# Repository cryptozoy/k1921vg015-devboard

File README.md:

# К1921ВГ015 DEVBOARD

Проект печатной платы для микроконтроллера К1921ВГ015 разработанный в KiCad 9.

Пожалуйста учитывайте, что фото может незначительно отличаться от платы в проекте, поскольку туда могут вноситься мелкие исправления.

Если вы хотите последнюю версию гербер файлов - рекомендуется формировать их самим, что гарантирует их актуальность.

Файлы сверловки экспортированы с настройками по умолчанию и лежат в `/gerber/`

Требования для 5$ в nextPCB были учтены и лично мной проверены.

Огромное спасибо: [@cryptozoy](https://github.com/cryptozoy) за доработку платы.

Все пины контроллера задействованы, все функциональные пины выведены на гребёнки:

 - Порты ABC

 - Функциональные пины и коммуникация

Файлы для генерации пинаутов лежат в папке `pinouts`

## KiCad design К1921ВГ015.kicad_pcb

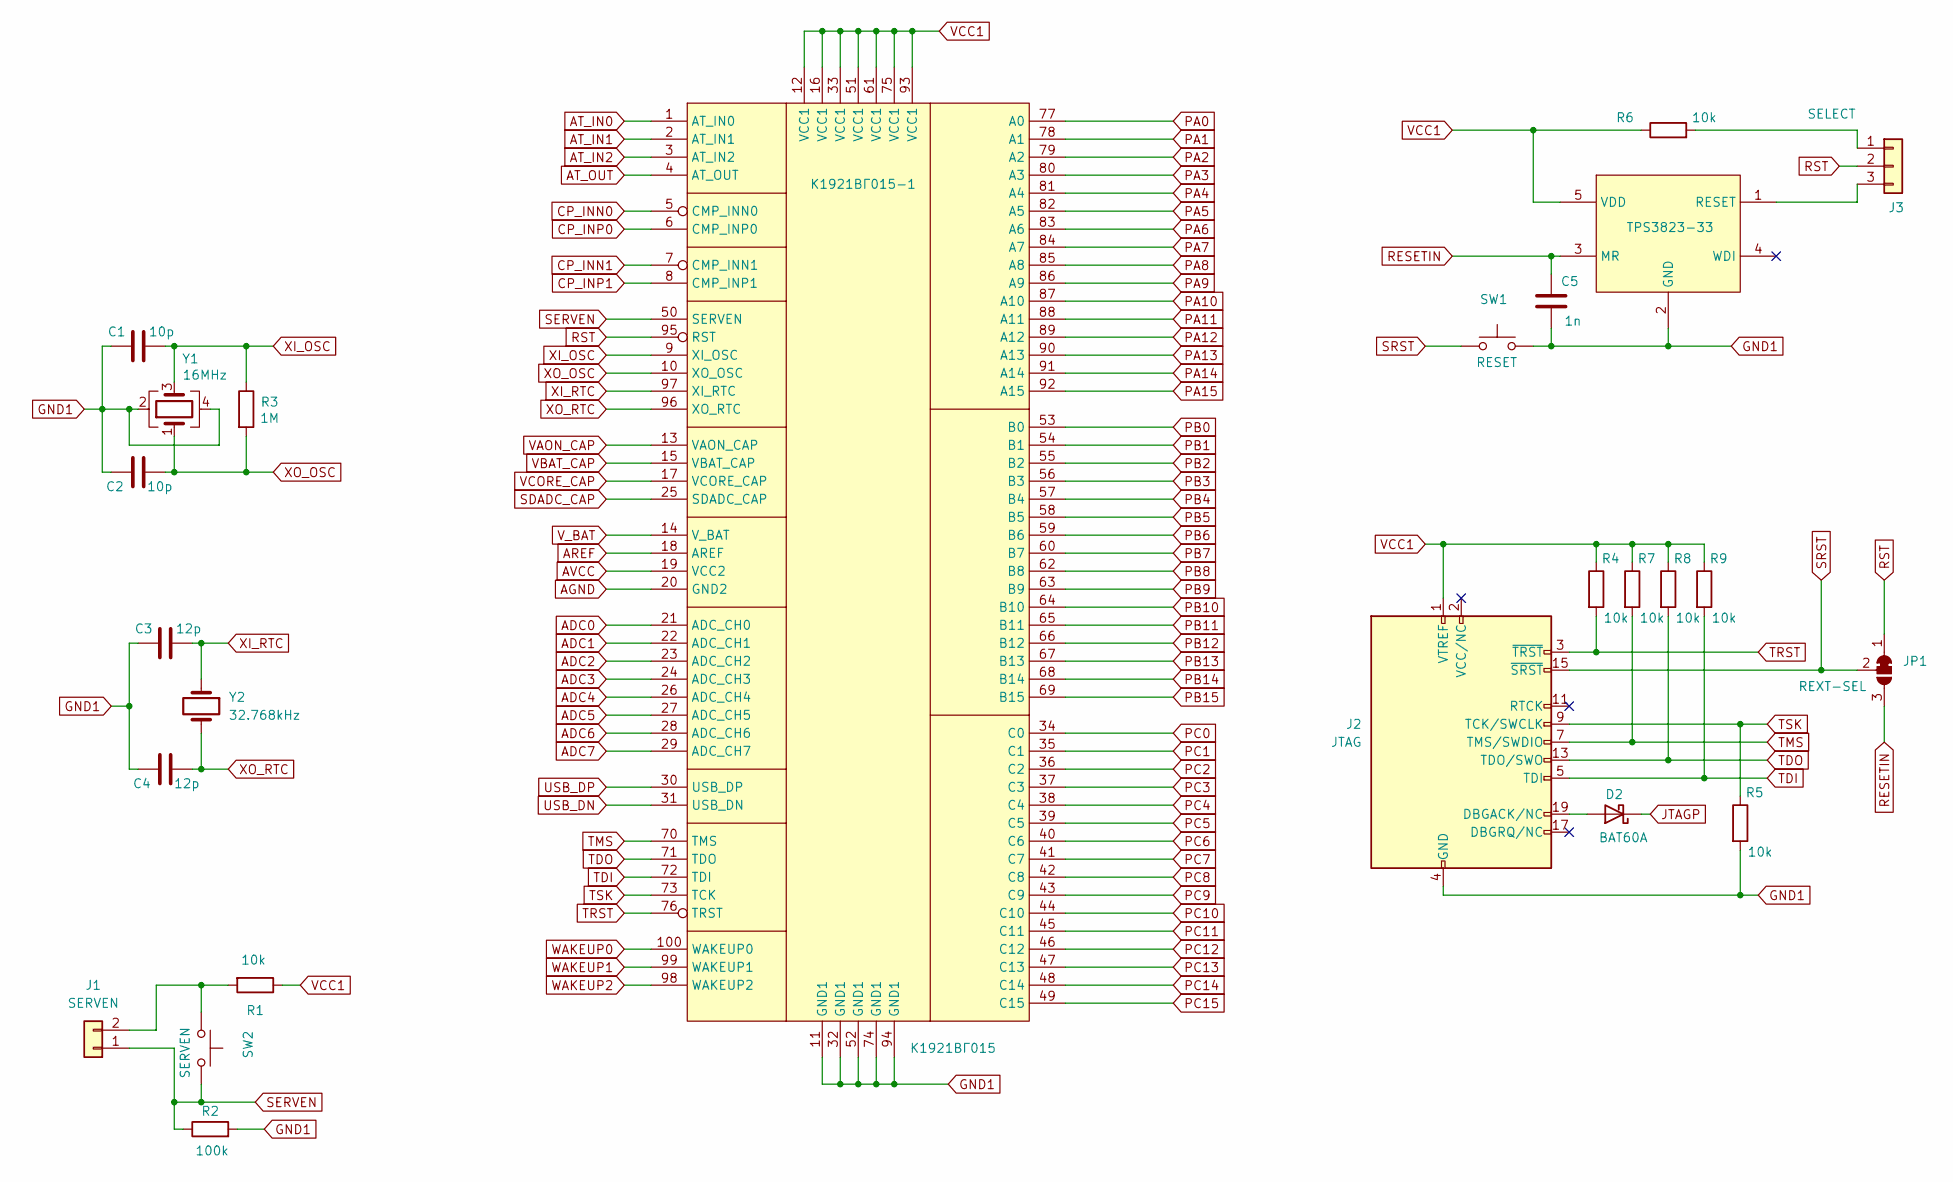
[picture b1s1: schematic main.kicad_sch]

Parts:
C1, C2: 10p; C_0805_2012Metric
C3, C4: 12p; C_0805_2012Metric
C5: 1n; C_0805_2012Metric
D2: BAT60A; D_SOD-323
J1: SERVEN; PinHeader_1x02_P2.54mm_Vertical
J2: JTAG; PinHeader_2x10_P2.54mm_Vertical
J3: SELECT; PinHeader_1x03_P2.54mm_Vertical
JP1: REXT-SEL; SolderJumper-3_P2.0mm_Open_TrianglePad1.0x1.5mm
R1, R4, R5, R6, R7, R8, R9: 10k; R_0805_2012Metric
R2: 100k; R_0805_2012Metric
R3: 1M; R_0805_2012Metric
SW1: RESET; SW_SPST_PTS647_Sx38
SW2: SERVEN; SW_SPST_PTS647_Sx38
TPS3823-1: TPS3823-33; SOT-23-5
Y1: 16MHz; Crystal_SMD_3225-4Pin_3.2x2.5mm
Y2: 32.768kHz; Crystal_SMD_3215-2Pin_3.2x1.5mm
К1921ВГ015-1: К1921ВГ015; LQFP-100_14x14mm_P0.5mm

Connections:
ADC0: К1921ВГ015-1.21 (ADC_CH0); also elsewhere on the board
ADC1: К1921ВГ015-1.22 (ADC_CH1); also elsewhere on the board
ADC2: К1921ВГ015-1.23 (ADC_CH2); also elsewhere on the board
ADC3: К1921ВГ015-1.24 (ADC_CH3); also elsewhere on the board
ADC4: К1921ВГ015-1.26 (ADC_CH4); also elsewhere on the board
ADC5: К1921ВГ015-1.27 (ADC_CH5); also elsewhere on the board
ADC6: К1921ВГ015-1.28 (ADC_CH6); also elsewhere on the board
ADC7: К1921ВГ015-1.29 (ADC_CH7); also elsewhere on the board
AGND: К1921ВГ015-1.20 (GND2); also elsewhere on the board
AREF: К1921ВГ015-1.18 (AREF); also elsewhere on the board
AT_IN0: К1921ВГ015-1.1 (AT_IN0); also elsewhere on the board
AT_IN1: К1921ВГ015-1.2 (AT_IN1); also elsewhere on the board
AT_IN2: К1921ВГ015-1.3 (AT_IN2); also elsewhere on the board
AT_OUT: К1921ВГ015-1.4 (AT_OUT); also elsewhere on the board
AVCC: К1921ВГ015-1.19 (VCC2); also elsewhere on the board
CAN0_RX: К1921ВГ015-1.42 (C8); also elsewhere on the board
CAN0_TX: К1921ВГ015-1.43 (C9); also elsewhere on the board
CAN1_RX: К1921ВГ015-1.44 (C10); also elsewhere on the board
CAN1_TX: К1921ВГ015-1.45 (C11); also elsewhere on the board
CP_INN0: К1921ВГ015-1.5 (CMP_INN0); also elsewhere on the board
CP_INN1: К1921ВГ015-1.7 (CMP_INN1); also elsewhere on the board
CP_INP0: К1921ВГ015-1.6 (CMP_INP0); also elsewhere on the board
CP_INP1: К1921ВГ015-1.8 (CMP_INP1); also elsewhere on the board
GND1: C1.2, C2.2, C3.2, C4.2, C5.2, J2.4 (GND), J2.6 (GND), J2.8 (GND), J2.10 (GND), J2.12 (GND), J2.14 (GND), J2.16 (GND), J2.18 (GND), J2.20 (GND), R2.2, R5.2, SW1.2, TPS3823-1.2 (GND), Y1.2, Y1.4, К1921ВГ015-1.11 (GND1), К1921ВГ015-1.32 (GND1), К1921ВГ015-1.52 (GND1), К1921ВГ015-1.74 (GND1), К1921ВГ015-1.94 (GND1); also elsewhere on the board
I2C_SCL: К1921ВГ015-1.46 (C12); also elsewhere on the board
I2C_SDA: К1921ВГ015-1.47 (C13); also elsewhere on the board
unnamed: D2.2 (A), J2.19 (DBGACK/NC)
unnamed: J1.2, R1.2, SW2.1
unnamed: J3.1, R6.2
unnamed: J3.3, TPS3823-1.1 (RESET)
PA0: К1921ВГ015-1.77 (A0); also elsewhere on the board
PA1: К1921ВГ015-1.78 (A1); also elsewhere on the board
PA2: К1921ВГ015-1.79 (A2); also elsewhere on the board
PA3: К1921ВГ015-1.80 (A3); also elsewhere on the board
PA4: К1921ВГ015-1.81 (A4); also elsewhere on the board
PA5: К1921ВГ015-1.82 (A5); also elsewhere on the board
PA6: К1921ВГ015-1.83 (A6); also elsewhere on the board
PA7: К1921ВГ015-1.84 (A7); also elsewhere on the board
PA8: К1921ВГ015-1.85 (A8); also elsewhere on the board
PA9: К1921ВГ015-1.86 (A9); also elsewhere on the board
PA10: К1921ВГ015-1.87 (A10); also elsewhere on the board
PA11: К1921ВГ015-1.88 (A11); also elsewhere on the board
PA12: К1921ВГ015-1.89 (A12); also elsewhere on the board
PA13: К1921ВГ015-1.90 (A13); also elsewhere on the board
PA14: К1921ВГ015-1.91 (A14); also elsewhere on the board
PA15: К1921ВГ015-1.92 (A15); also elsewhere on the board
PB0: К1921ВГ015-1.53 (B0); also elsewhere on the board
PB1: К1921ВГ015-1.54 (B1); also elsewhere on the board
PB2: К1921ВГ015-1.55 (B2); also elsewhere on the board
PB3: К1921ВГ015-1.56 (B3); also elsewhere on the board
PB4: К1921ВГ015-1.57 (B4); also elsewhere on the board
PB5: К1921ВГ015-1.58 (B5); also elsewhere on the board
PB6: К1921ВГ015-1.59 (B6); also elsewhere on the board
PB7: К1921ВГ015-1.60 (B7); also elsewhere on the board
PB8: К1921ВГ015-1.62 (B8); also elsewhere on the board
PB9: К1921ВГ015-1.63 (B9); also elsewhere on the board
PB10: К1921ВГ015-1.64 (B10); also elsewhere on the board
PB11: К1921ВГ015-1.65 (B11); also elsewhere on the board
PB12: К1921ВГ015-1.66 (B12); also elsewhere on the board
PB13: К1921ВГ015-1.67 (B13); also elsewhere on the board
PB14: К1921ВГ015-1.68 (B14); also elsewhere on the board
PB15: К1921ВГ015-1.69 (B15); also elsewhere on the board
PC0: К1921ВГ015-1.34 (C0); also elsewhere on the board
PC1: К1921ВГ015-1.35 (C1); also elsewhere on the board
PC2: К1921ВГ015-1.36 (C2); also elsewhere on the board
PC3: К1921ВГ015-1.37 (C3); also elsewhere on the board
PC4: К1921ВГ015-1.38 (C4); also elsewhere on the board
PC5: К1921ВГ015-1.39 (C5); also elsewhere on the board
PC6: К1921ВГ015-1.40 (C6); also elsewhere on the board
PC7: К1921ВГ015-1.41 (C7); also elsewhere on the board
PC14: К1921ВГ015-1.48 (C14); also elsewhere on the board
PC15: К1921ВГ015-1.49 (C15); also elsewhere on the board
PJTAG: D2.1 (K); also elsewhere on the board
RESETIN: C5.1, JP1.3 (B), TPS3823-1.3 (MR)
RST: J3.2, JP1.1 (A), К1921ВГ015-1.95 (RST)
SDADC_CAP: К1921ВГ015-1.25 (SDADC_CAP); also elsewhere on the board
SERVEN: J1.1, R2.1, SW2.2, К1921ВГ015-1.50 (SERVEN)
SRST: J2.15 (~SRST), JP1.2 (C), SW1.1
TDI: J2.5 (TDI), R9.2, К1921ВГ015-1.72 (TDI)
TDO: J2.13 (TDO/SWO), R8.2, К1921ВГ015-1.71 (TDO)
TMS: J2.7 (TMS/SWDIO), R7.2, К1921ВГ015-1.70 (TMS)
TRST: J2.3 (~TRST), R4.2, К1921ВГ015-1.76 (TRST)
TSK: J2.9 (TCK/SWCLK), R5.1, К1921ВГ015-1.73 (TCK)
USB_DN: К1921ВГ015-1.31 (USB_DN); also elsewhere on the board
USB_DP: К1921ВГ015-1.30 (USB_DP); also elsewhere on the board
VAON_CAP: К1921ВГ015-1.13 (VAON_CAP); also elsewhere on the board
VBAT_CAP: К1921ВГ015-1.15 (VBAT_CAP); also elsewhere on the board
VCC1: J2.1 (VTREF), R1.1, R4.1, R6.1, R7.1, R8.1, R9.1, TPS3823-1.5 (VDD), К1921ВГ015-1.12 (VCC1), К1921ВГ015-1.16 (VCC1), К1921ВГ015-1.33 (VCC1), К1921ВГ015-1.51 (VCC1), К1921ВГ015-1.61 (VCC1), К1921ВГ015-1.75 (VCC1), К1921ВГ015-1.93 (VCC1); also elsewhere on the board
VCORE_CAP: К1921ВГ015-1.17 (VCORE_CAP); also elsewhere on the board
V_BAT: К1921ВГ015-1.14 (V_BAT); also elsewhere on the board
WAKEUP0: К1921ВГ015-1.100 (WAKEUP0); also elsewhere on the board
WAKEUP1: К1921ВГ015-1.99 (WAKEUP1); also elsewhere on the board
WAKEUP2: К1921ВГ015-1.98 (WAKEUP2); also elsewhere on the board
XI_OSC: C1.1, R3.1, Y1.3, К1921ВГ015-1.9 (XI_OSC)
XI_RTC: C3.1, Y2.1, К1921ВГ015-1.97 (XI_RTC)
XO_OSC: C2.1, R3.2, Y1.1, К1921ВГ015-1.10 (XO_OSC)
XO_RTC: C4.1, Y2.2, К1921ВГ015-1.96 (XO_RTC)

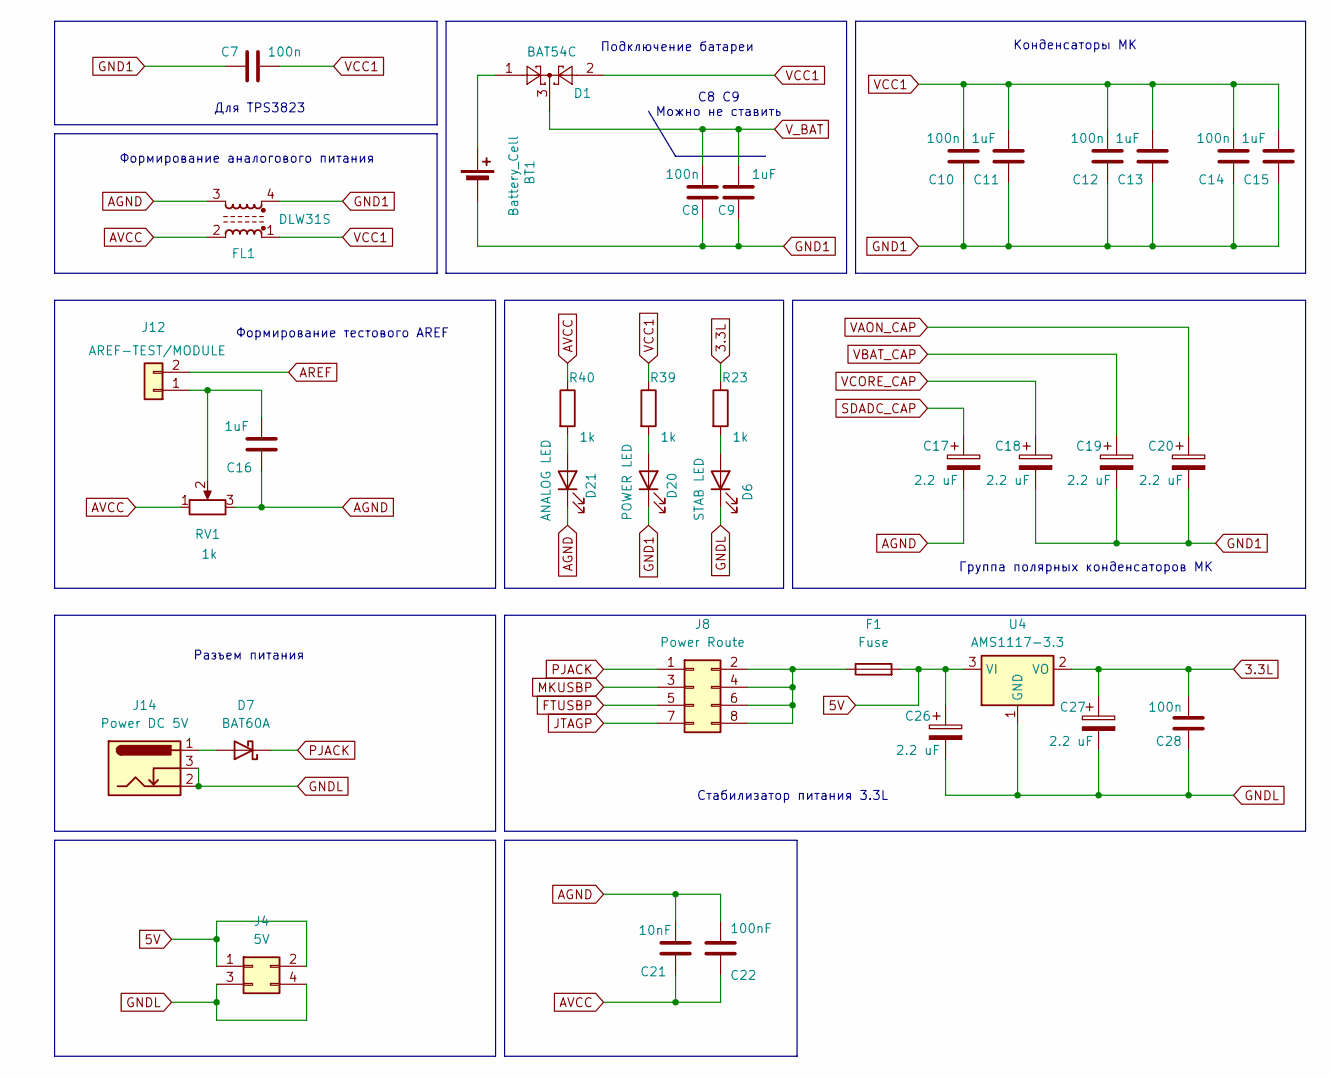
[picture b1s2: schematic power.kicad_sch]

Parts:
BT1: Battery_Cell; Battery_Panasonic_CR2032-HFN_Horizontal_CircularHoles
C7, C8, C10, C12, C14, C28: 100n; C_0805_2012Metric
C9, C11, C13, C15, C16: 1uF; C_0805_2012Metric
C17, C18, C19, C20, C26, C27: 2.2 uF; CP_EIA-3528-21_Kemet-B
C21: 10nF; C_0805_2012Metric
C22: 100nF; C_0805_2012Metric
D1: BAT54C; SOT-23
D6: STAB LED; LED_0805_2012Metric
D7: BAT60A; D_SOD-323
D20: POWER LED; LED_0805_2012Metric
D21: ANALOG LED; LED_0805_2012Metric
F1: Fuse; Fuse_1812_4532Metric
FL1: DLW31S; L_CommonMode_Wurth_WE-CNSW-1206
J4: 5V; PinHeader_2x02_P2.54mm_Vertical
J8: Power Route; PinHeader_2x04_P2.54mm_Vertical
J12: AREF-TEST/MODULE; PinHeader_1x02_P2.54mm_Vertical
J14: Power DC 5V; BarrelJack_GCT_DCJ200-10-A_Horizontal
R23, R39, R40: 1k; R_0805_2012Metric
RV1: 1k; Potentiometer_Bourns_3296W_Vertical
U4: AMS1117-3.3; SOT-223-3_TabPin2

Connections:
3.3L: C27.1, C28.1, R23.1, U4.2 (VO); also elsewhere on the board
5V: C26.1, F1.2, J4.1, J4.2, U4.3 (VI)
AGND: C16.2, C17.2, C21.1, C22.1, D21.1 (K), FL1.3, RV1.3; also elsewhere on the board
AREF: J12.2; also elsewhere on the board
AVCC: C21.2, C22.2, FL1.2, R40.1, RV1.1; also elsewhere on the board
FTUSBP: J8.5; also elsewhere on the board
GND1: BT1.2 (-), C7.2, C8.2, C9.2, C10.2, C11.2, C12.2, C13.2, C14.2, C15.2, C18.2, C19.2, C20.2, D20.1 (K), FL1.4; also elsewhere on the board
GNDL: C26.2, C27.2, C28.2, D6.1 (K), J4.3, J4.4, J14.2, J14.3, U4.1 (GND); also elsewhere on the board
MKUSBP: J8.3; also elsewhere on the board
unnamed: BT1.1 (+), D1.1
unnamed: D6.2 (A), R23.2
unnamed: D7.2 (A), J14.1
unnamed: D20.2 (A), R39.2
unnamed: D21.2 (A), R40.2
unnamed: F1.1, J8.2, J8.4, J8.6, J8.8
unnamed: C16.1, J12.1, RV1.2
PJACK: D7.1 (K), J8.1
PJTAG: J8.7; also elsewhere on the board
SDADC_CAP: C17.1; also elsewhere on the board
VAON_CAP: C20.1; also elsewhere on the board
VBAT_CAP: C19.1; also elsewhere on the board
VCC1: C7.1, C10.1, C11.1, C12.1, C13.1, C14.1, C15.1, D1.2, FL1.1, R39.1; also elsewhere on the board
VCORE_CAP: C18.1; also elsewhere on the board
V_BAT: C8.1, C9.1, D1.3; also elsewhere on the board

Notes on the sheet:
Группа полярных конденсаторов МК
Формирование аналогового питания
Формирование тестового AREF
Подключение батареи
Конденсаторы МК
Для TPS3823
Разъем питания
С8 C9 Можно не ставить
Стабилизатор питания 3.3L

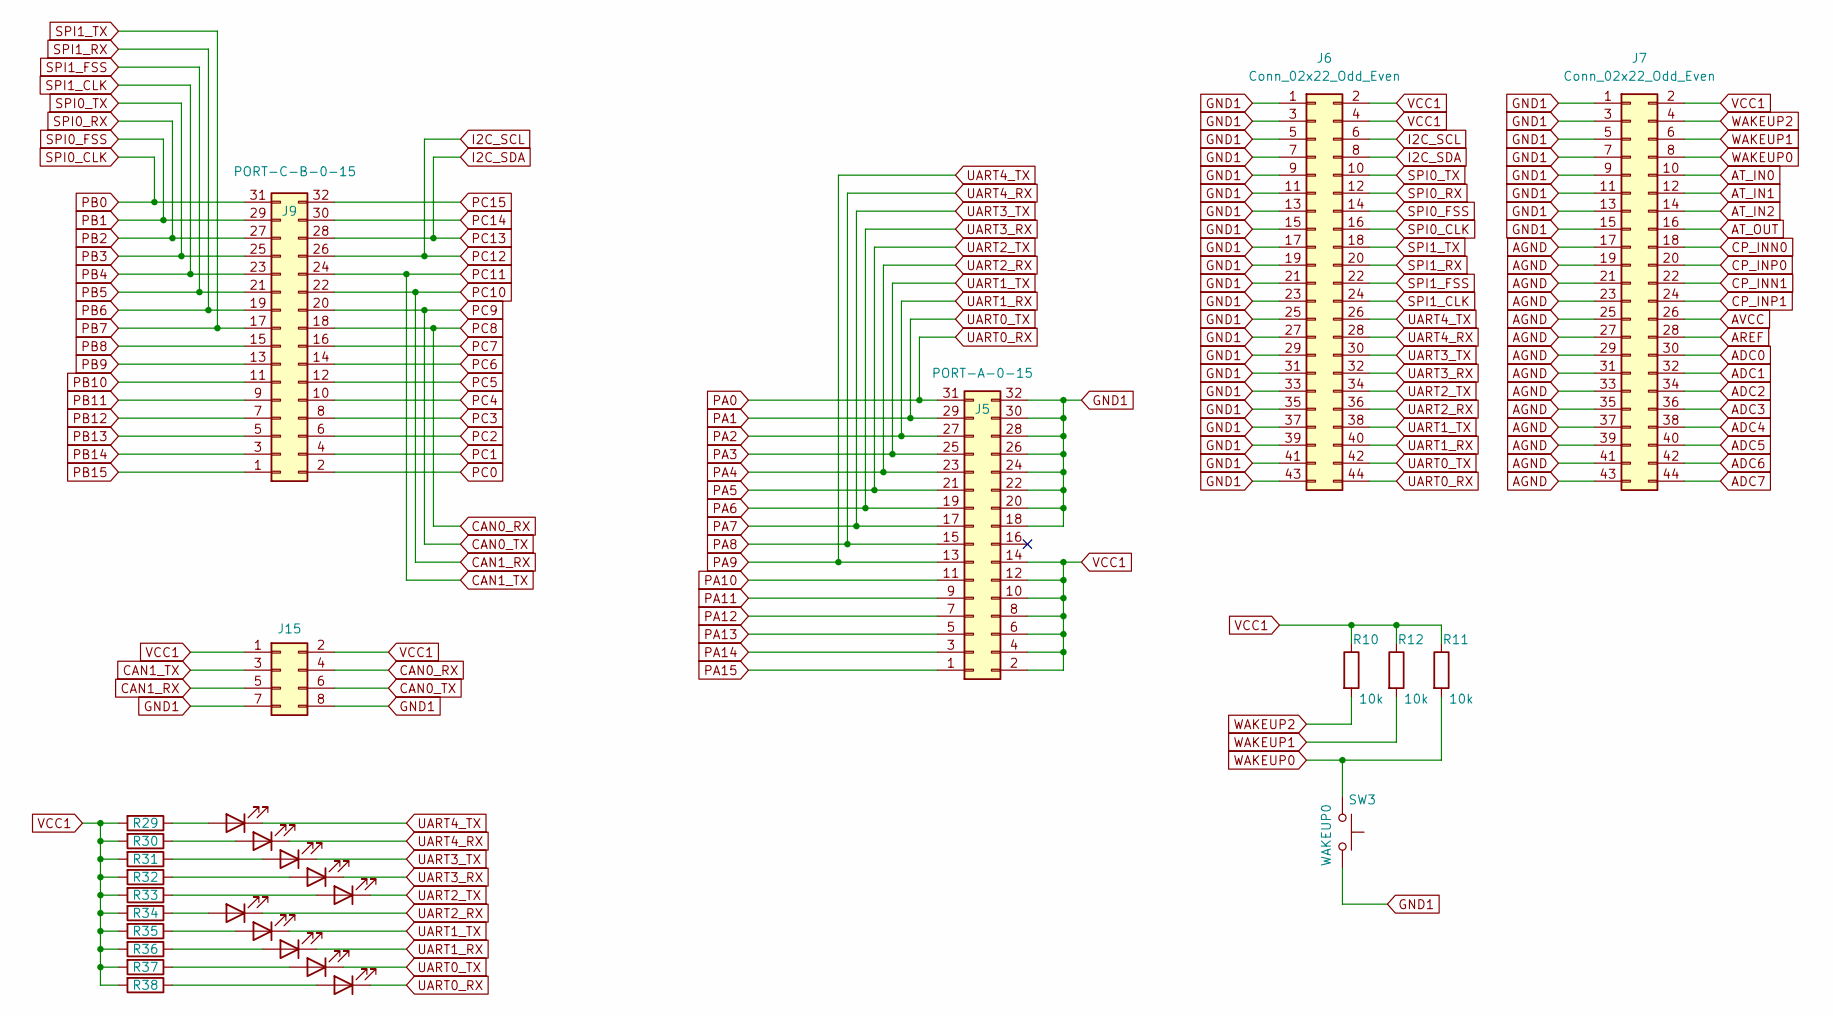
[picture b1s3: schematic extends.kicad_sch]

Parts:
D10: U4TX; LED_0805_2012Metric
D11: U4RX; LED_0805_2012Metric
D12: U3TX; LED_0805_2012Metric
D13: U3RX; LED_0805_2012Metric
D14: U2TX; LED_0805_2012Metric
D15: U1TX; LED_0805_2012Metric
D16: U1RX; LED_0805_2012Metric
D17: U0TX; LED_0805_2012Metric
D18: U0RX; LED_0805_2012Metric
D19: U2RX; LED_0805_2012Metric
J5: PORT-A-0-15; PinHeader_2x16_P2.54mm_Vertical
J6, J7: Conn_02x22_Odd_Even; PinHeader_2x22_P2.54mm_Vertical
J9: PORT-C-B-0-15; PinHeader_2x16_P2.54mm_Vertical
J15: Conn_02x04_Odd_Even; PinHeader_2x04_P2.54mm_Vertical
R10, R11, R12: 10k; R_0805_2012Metric
R29, R30, R31, R32, R33, R34, R35, R36, R37, R38: 1k; R_0805_2012Metric
SW3: WAKEUP0; SW_SPST_PTS647_Sx38

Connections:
ADC0: J7.30; also elsewhere on the board
ADC1: J7.32; also elsewhere on the board
ADC2: J7.34; also elsewhere on the board
ADC3: J7.36; also elsewhere on the board
ADC4: J7.38; also elsewhere on the board
ADC5: J7.40; also elsewhere on the board
ADC6: J7.42; also elsewhere on the board
ADC7: J7.44; also elsewhere on the board
AGND: J7.17, J7.19, J7.21, J7.23, J7.25, J7.27, J7.29, J7.31, J7.33, J7.35, J7.37, J7.39, J7.41, J7.43; also elsewhere on the board
AREF: J7.28; also elsewhere on the board
AT_IN0: J7.10; also elsewhere on the board
AT_IN1: J7.12; also elsewhere on the board
AT_IN2: J7.14; also elsewhere on the board
AT_OUT: J7.16; also elsewhere on the board
AVCC: J7.26; also elsewhere on the board
CAN0_RX: J9.18, J15.4; also elsewhere on the board
CAN0_TX: J9.20, J15.6; also elsewhere on the board
CAN1_RX: J9.22, J15.5; also elsewhere on the board
CAN1_TX: J9.24, J15.3; also elsewhere on the board
CP_INN0: J7.18; also elsewhere on the board
CP_INN1: J7.22; also elsewhere on the board
CP_INP0: J7.20; also elsewhere on the board
CP_INP1: J7.24; also elsewhere on the board
GND1: J5.18, J5.20, J5.22, J5.24, J5.26, J5.28, J5.30, J5.32, J6.1, J6.3, J6.5, J6.7, J6.9, J6.11, J6.13, J6.15, J6.17, J6.19, J6.21, J6.23, J6.25, J6.27, J6.29, J6.31, J6.33, J6.35, J6.37, J6.39, J6.41, J6.43, J7.1, J7.3, J7.5, J7.7, J7.9, J7.11, J7.13, J7.15, J15.7, J15.8, SW3.2; also elsewhere on the board
I2C_SCL: J6.6, J9.26; also elsewhere on the board
I2C_SDA: J6.8, J9.28; also elsewhere on the board
unnamed: D10.2 (A), R29.1
unnamed: D11.2 (A), R30.1
unnamed: D12.2 (A), R31.1
unnamed: D13.2 (A), R32.1
unnamed: D14.2 (A), R33.1
unnamed: D15.2 (A), R35.1
unnamed: D16.2 (A), R36.1
unnamed: D17.2 (A), R37.1
unnamed: D18.2 (A), R38.1
unnamed: D19.2 (A), R34.1
PA0: D18.1 (K), J5.31, J6.44; also elsewhere on the board
PA1: D17.1 (K), J5.29, J6.42; also elsewhere on the board
PA2: D16.1 (K), J5.27, J6.40; also elsewhere on the board
PA3: D15.1 (K), J5.25, J6.38; also elsewhere on the board
PA4: D19.1 (K), J5.23, J6.36; also elsewhere on the board
PA5: D14.1 (K), J5.21, J6.34; also elsewhere on the board
PA6: D13.1 (K), J5.19, J6.32; also elsewhere on the board
PA7: D12.1 (K), J5.17, J6.30; also elsewhere on the board
PA8: D11.1 (K), J5.15, J6.28; also elsewhere on the board
PA9: D10.1 (K), J5.13, J6.26; also elsewhere on the board
PA10: J5.11; also elsewhere on the board
PA11: J5.9; also elsewhere on the board
PA12: J5.7; also elsewhere on the board
PA13: J5.5; also elsewhere on the board
PA14: J5.3; also elsewhere on the board
PA15: J5.1; also elsewhere on the board
PB0: J6.16, J9.31; also elsewhere on the board
PB1: J6.14, J9.29; also elsewhere on the board
PB2: J6.12, J9.27; also elsewhere on the board
PB3: J6.10, J9.25; also elsewhere on the board
PB4: J6.24, J9.23; also elsewhere on the board
PB5: J6.22, J9.21; also elsewhere on the board
PB6: J6.20, J9.19; also elsewhere on the board
PB7: J6.18, J9.17; also elsewhere on the board
PB8: J9.15; also elsewhere on the board
PB9: J9.13; also elsewhere on the board
PB10: J9.11; also elsewhere on the board
PB11: J9.9; also elsewhere on the board
PB12: J9.7; also elsewhere on the board
PB13: J9.5; also elsewhere on the board
PB14: J9.3; also elsewhere on the board
PB15: J9.1; also elsewhere on the board
PC0: J9.2; also elsewhere on the board
PC1: J9.4; also elsewhere on the board
PC2: J9.6; also elsewhere on the board
PC3: J9.8; also elsewhere on the board
PC4: J9.10; also elsewhere on the board
PC5: J9.12; also elsewhere on the board
PC6: J9.14; also elsewhere on the board
PC7: J9.16; also elsewhere on the board
PC14: J9.30; also elsewhere on the board
PC15: J9.32; also elsewhere on the board
VCC1: J5.2, J5.4, J5.6, J5.8, J5.10, J5.12, J5.14, J6.2, J6.4, J7.2, J15.1, J15.2, R10.1, R11.1, R12.1, R29.2, R30.2, R31.2, R32.2, R33.2, R34.2, R35.2, R36.2, R37.2, R38.2; also elsewhere on the board
WAKEUP0: J7.8, R11.2, SW3.1; also elsewhere on the board
WAKEUP1: J7.6, R12.2; also elsewhere on the board
WAKEUP2: J7.4, R10.2; also elsewhere on the board

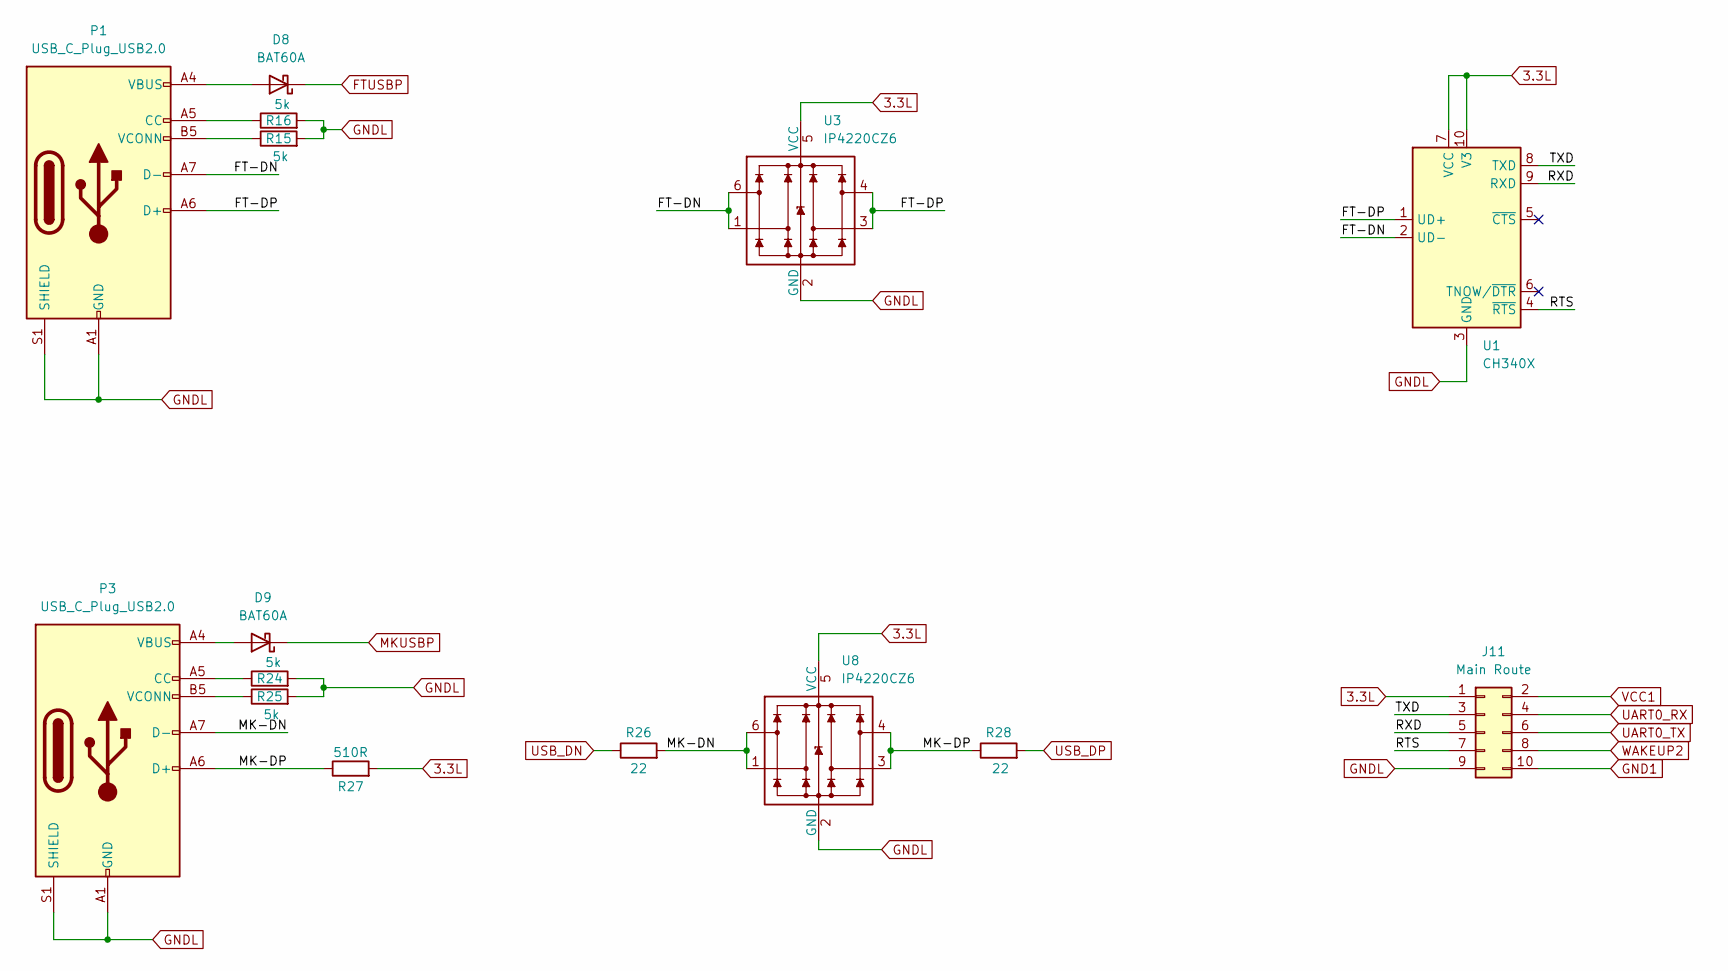
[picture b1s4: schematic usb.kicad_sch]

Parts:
D8, D9: BAT60A; D_SOD-323
J11: Main Route; PinHeader_2x05_P2.54mm_Vertical
P1, P3: USB_C_Plug_USB2.0; USB_C_Receptacle_HRO_TYPE-C-31-M-12
R15, R16, R24, R25: 5k; R_0805_2012Metric
R26, R28: 22; R_0805_2012Metric
R27: 510R; R_0805_2012Metric
U1: CH340X; MSOP-10_3x3mm_P0.5mm
U3, U8: IP4220CZ6; SC-74-6_1.55x2.9mm_P0.95mm

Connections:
3.3L: J11.1, R27.2, U1.7 (VCC), U1.10 (V3), U3.5 (VCC), U8.5 (VCC); also elsewhere on the board
/USB/FT-DN: P1.A7 (D-), U1.2 (UD-), U3.1, U3.6
/USB/FT-DP: P1.A6 (D+), U1.1 (UD+), U3.3, U3.4
/USB/MK-DN: P3.A7 (D-), R26.2, U8.1, U8.6
/USB/MK-DP: P3.A6 (D+), R27.1, R28.1, U8.3, U8.4
/USB/RTS: J11.7, U1.4 (~RTS)
/USB/RXD: J11.5, U1.9 (RXD)
/USB/TXD: J11.3, U1.8 (TXD)
FTUSBP: D8.1 (K); also elsewhere on the board
GND1: J11.10; also elsewhere on the board
GNDL: J11.9, P1.A1 (GND), P1.A12 (GND), P1.B1 (GND), P1.B12 (GND), P1.S1 (SHIELD), P3.A1 (GND), P3.A12 (GND), P3.B1 (GND), P3.B12 (GND), P3.S1 (SHIELD), R15.2, R16.2, R24.2, R25.2, U1.3 (GND), U3.2 (GND), U8.2 (GND); also elsewhere on the board
MKUSBP: D9.1 (K); also elsewhere on the board
unnamed: D8.2 (A), P1.A4 (VBUS), P1.A9 (VBUS), P1.B4 (VBUS), P1.B9 (VBUS)
unnamed: D9.2 (A), P3.A4 (VBUS), P3.A9 (VBUS), P3.B4 (VBUS), P3.B9 (VBUS)
unnamed: P1.A5 (CC), R16.1
unnamed: P1.B5 (VCONN), R15.1
unnamed: P3.A5 (CC), R24.1
unnamed: P3.B5 (VCONN), R25.1
PA0: J11.4; also elsewhere on the board
PA1: J11.6; also elsewhere on the board
USB_DN: R26.1; also elsewhere on the board
USB_DP: R28.2; also elsewhere on the board
VCC1: J11.2; also elsewhere on the board
WAKEUP2: J11.8; also elsewhere on the board

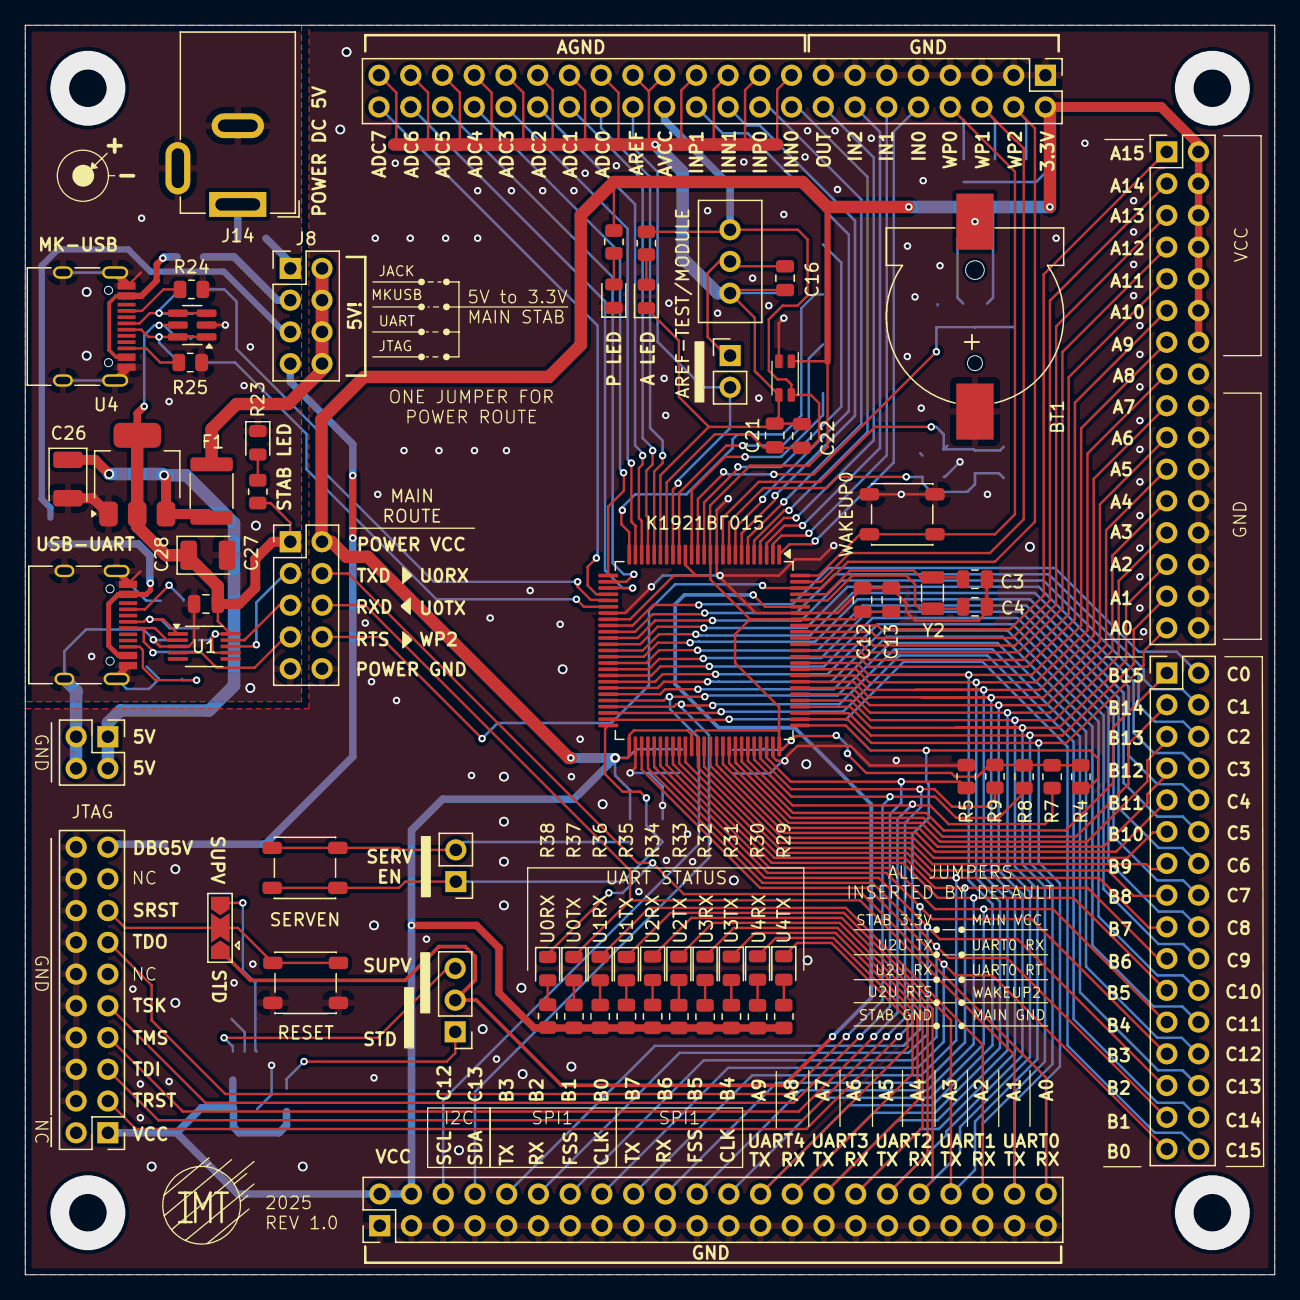
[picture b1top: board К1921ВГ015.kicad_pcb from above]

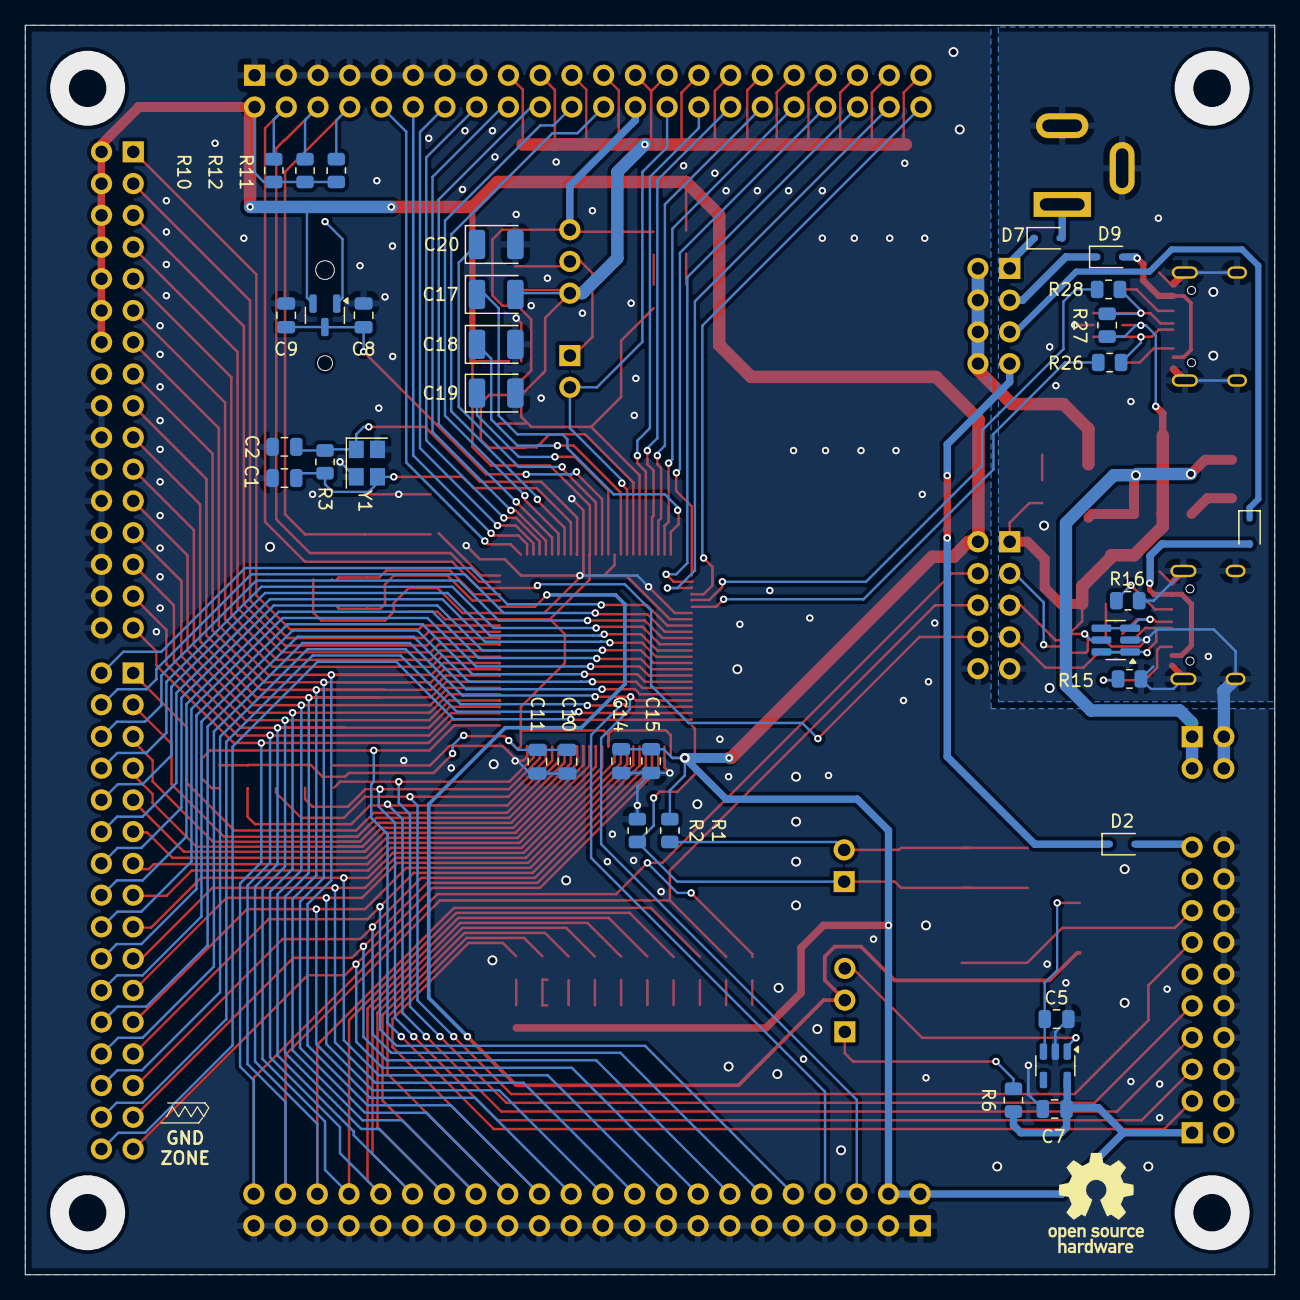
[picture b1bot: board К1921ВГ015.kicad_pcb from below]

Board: 2 copper layers, 100.0 x 100.0 mm, 104 parts (34 on the bottom side), 133 nets.

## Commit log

2025-05-15 INIT
2025-05-16 Add AGND capacitors
2025-05-16 Update APower
2025-05-18 3D-модели предохранителя и фильтра
2025-05-19 Обновление 3D моделей от cryptozoy
2025-05-19 3D модели разъёмов питания и USB
2025-05-19 Еще обновление 3D моделей от cryptozoy
    Обновление Barrel Jack + TypeC
2025-05-20 Питание 5V от JTAG, множественные исправления
2025-05-20 Update gerber & drl files
2025-05-23 Обновление изображений
2025-05-23 Установочное место и 3D-модель держателя батареи
2025-05-23 Обновление платы
